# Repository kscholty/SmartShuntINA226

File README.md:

## Overview
This project uses an INA226 shunt amplifier to implement some smart shunt functionality.
It sums up the charges that move through the shunt. With this information it tries to calculate the load status of an attached battery.
The INA226 should be connected to the shunt so that charges going into the battery are positive and those coming out of the battery are negtive.

The smart shunt has three main interfaces.

1) A web interface for human users. It allows setting the main parameters of the system and displays the current status of the system
2) A modbus interface that is based on a PZEM017 energy meter but enhances it with the values mentioned above
3) Victron VE.direct Text and Hex protocols in order to function as a Battery Monitor. The Hex protocol is only implemented as far as it's required for startup. Furthermore, some fields of the Text protocol are not yet filled correctly.

## Building the code yourself
The Software has been created using platformio and the Arduino environment. In order to build it you als need some libraries.
* the [INA226lib](https://github.com/peterus/INA226Lib) The latest version should work with this code.
* emelianov/modbus-esp8266
* locoduino/RingBuffer
* prampec/IotWebConf

The latter three will be automatically downloaded when using platformio.

## Required hardware

For measuring the current you need an __INA226 breakout board__ as you can acquire from 
[Amazon](https://www.amazon.de/ALAMSCN-Bi-Directional-Voltage-Current-Monitoring/dp/B09Z66QSPB/ref=sr_1_4?keywords=ina226&qid=1674921078&sr=8-4),
[Ebay](https://www.ebay.de/itm/403798012528?mkcid=16&mkevt=1&mkrid=707-127634-2357-0&ssspo=3VTGCNeFTJm&sssrc=2047675&ssuid=0YZwUxrsQgu&widget_ver=artemis&media=COPY) or [AliExpress](https://de.aliexpress.com/item/1005001593541480.html?spm=a2g0o.productlist.main.3.56f351729HIcrL&algo_pvid=355d9f06-c6bf-45e7-922c-611aa36108cf&algo_exp_id=355d9f06-c6bf-45e7-922c-611aa36108cf-1&pdp_ext_f=%7B%22sku_id%22%3A%2212000016714954183%22%7D&pdp_npi=2%40dis%21EUR%213.22%212.06%21%21%21%21%21%402145294416749211574187658d06b7%2112000016714954183%21sea&curPageLogUid=PnWeLZQyi9Cc)

I noticed that some of the boards have a different pinout. The SDA and SDL pins are swapped in comparison to others. So please check this if you can't get a connection to the sensor.

As __miocrocontroller__ I settled for Espressif products. This code has been tested with a Wemos D1 Mini, a Wemos S2 mini and a 8266 Nodemcu. I didn't test any ESP32 WROOM boards, but they should work too. I setteled for the S2 mini due to its small footprint and powerful CPU. I got mine from [Aliexpress](https://de.aliexpress.com/item/1005004438665554.html?spm=a2g0o.productlist.main.5.5ffa60aafadABW&algo_pvid=dd20a2a6-e95b-45fa-a21f-18e0922615da&algo_exp_id=dd20a2a6-e95b-45fa-a21f-18e0922615da-2&pdp_ext_f=%7B%22sku_id%22%3A%2212000029182790427%22%7D&pdp_npi=2%40dis%21EUR%212.72%212.23%21%21%21%21%21%402145274c16754348326558450d06ca%2112000029182790427%21sea&curPageLogUid=wBPd7zKYNEX1)

You also need a __shunt__, since the small resistor on the board (dont forget to remove it!) will not survive the high currents of a PV plant.
There are plenty of options out there. Again [Aliexpress](https://de.aliexpress.com/item/1005001678592758.html?spm=a2g0o.productlist.main.29.306d4ec19gJkAJ&algo_pvid=29bbcfa0-d3c6-4854-8a79-1bb33adbf3d4&aem_p4p_detail=2023020306362112631641799161540004060030&algo_exp_id=29bbcfa0-d3c6-4854-8a79-1bb33adbf3d4-14&pdp_ext_f=%7B%22sku_id%22%3A%2212000017093083607%22%7D&pdp_npi=2%40dis%21EUR%213.88%213.1%21%21%21%21%21%402100b84516754349819031656d0753%2112000017093083607%21sea&curPageLogUid=4Pyd35DHXJ61&ad_pvid=2023020306362112631641799161540004060030_4&ad_pvid=2023020306362112631641799161540004060030_4) or [Ebay](https://www.ebay.de/sch/i.html?_from=R40&_trksid=p2334524.m570.l1313&_nkw=shunt+resistor&_sacat=0&LH_TitleDesc=0&_odkw=shunt&_osacat=0) are probably the best sources.
Make sure that you select a resistor appropriate for the currents you expect. I'm using a 200A/75mV shunt.

I recommend using a __buck converter__ to create 5V for feeding the MCU and the sensor from the battery. 
Make sure Battery - is connected to the GND potential of the sensor. Otherwise the voltage measurements will be invalid, since the INA226 has only one GND.
Furthermore, you should use an __isolated USB module__ to connect the D1 to the target. You can destroy your computer or Victron GSX if you connect it directly to the USB of the MCU. [I use this one](https://www.ebay.de/itm/164934927888?mkcid=16&mkevt=1&mkrid=707-127634-2357-0&ssspo=k80Mu6A-TbK&sssrc=2047675&ssuid=0YZwUxrsQgu&widget_ver=artemis&media=COPY)

__Before you can use the sensor board you have to remove the shunt resistor soldered to that board and instead use a bigger shunt, e.g. a 100A/75mV.__
Make sure that the shunt supports the current your system produces. You can set the parameters of the shunt in the web interface.
A wide variety of shunts can be found on EBay or other platforms.

If you have a 48V System, be aware of the fact that the INA226 does only support voltages up to 36V (40V max). You need a voltage divider to make shure your sensor is not destroyed. 
The code assumes that you use a __470KOhm and a 1MOhm__ resistor, measuring across the 1MOhm towards GND. `( + --470K-- --1M -- GND )` This should work for a 16S LifePO4 battery. The smaller you choose the small resistor in comparison to the bigger one, the more accurate the measurement will be.

The configuration field `Voltage calibration factor` can be used to calibrate the voltage reading of the sensor. Set it to `1000` and then simply divide the real battery voltage by the value the sensor shows and multiply it by `1000`. 
The same can be done for the current in the field `Current calibration factor`. If you entered the shunt resistance correctly, a value close to 1000 is expected here. Mine is 1028.5.

The following image shows how to connect the parts.

## Interfaces:

1) Web Interface. 
    The web interface is quite self explanatory. It contains values to configure the shunt you are using. 
    Furthermore some that have been inspired by the Victron SmartShunt. 
2) Victron Text and Hex Protocols. These are decirbed on the  Victron Website and are mainly useful for connecting to Victron Cerbos or othe GX devices.
    Victron Device Type allow to declare Smart Shunt as a monitor for external load or supply: DC load, wind/water turbine, car alternator...
4)  The Modbus interface
    The Modbus interface uses 9600 Buad 8N2. The following registers are exposed
    - Holding registers (the first 4 are the ones from a PZEM-017)
    ```
        0: High Voltage alarm Threshold (not functional at the moment)
        1: Low Voltage alarm Threshold (not functional at the moment)
        2: Modbus Address
        3: Shunt Value (Refer to table below) what the values mean
        4: Identifier (This register contains the ID 0xBF39D to distinguish it from other sensors)
        5: Set SOC (Can be used to set an SOC, e.g. after startup)
    ```
    - Input Registers (again the first 8 are identical to the PZEM-017, however, here the current and power can be negative)
    ```
        0: Bus Voltage
        1: Current
        2: PowerLow (power low word)
        3: PowerHigh (power high word)
        4: EnergyLow (Energy low word)
        5: EnergyHigh (Energy high word)
        6: HighVoltageAlarm status (Is high voltage alarm set, not yet functional)
        7: LowVoltageAlarm status (Is high voltage alarm set, not yet functional)
        8: TimeToGoLow (LowWord of timeToGo in Seconds)
        9: TimeToGoHigh (HighWord of timeToGo in Seconds)
        10: SOC (Soc in %)
        11: isFull (1 if battery is detected to be full, 0 otherwise)
    ```

Shunt values for modbus, assumed is a voltage of 75mV at nominal current. 
The values are those used by PZEM-017.

```
Register Value | nominal current | Resulting resistance mR
0              |  100A           |  0.750
1              |   50A           |  1.500
2              |  200A           |  0.375
3              |  300A           |  0.250
```

When you start the sensor for the first time it will open an access point you can connect to in order to set wifi credentials and the other parameters.
After connecting to that access point, direct your browser to `http://192.168.4.1`. This will open the configuration page.
The sensor will always create that access point after startup. For how long can be configured. 

## Screenshots

## Remote console with Shunt

## Remote console details

## Remote console details for DC system

## Real setup with SmartShunt as a DC System

## Web config

## Web config for Victron Device Type

## Everything soldered together

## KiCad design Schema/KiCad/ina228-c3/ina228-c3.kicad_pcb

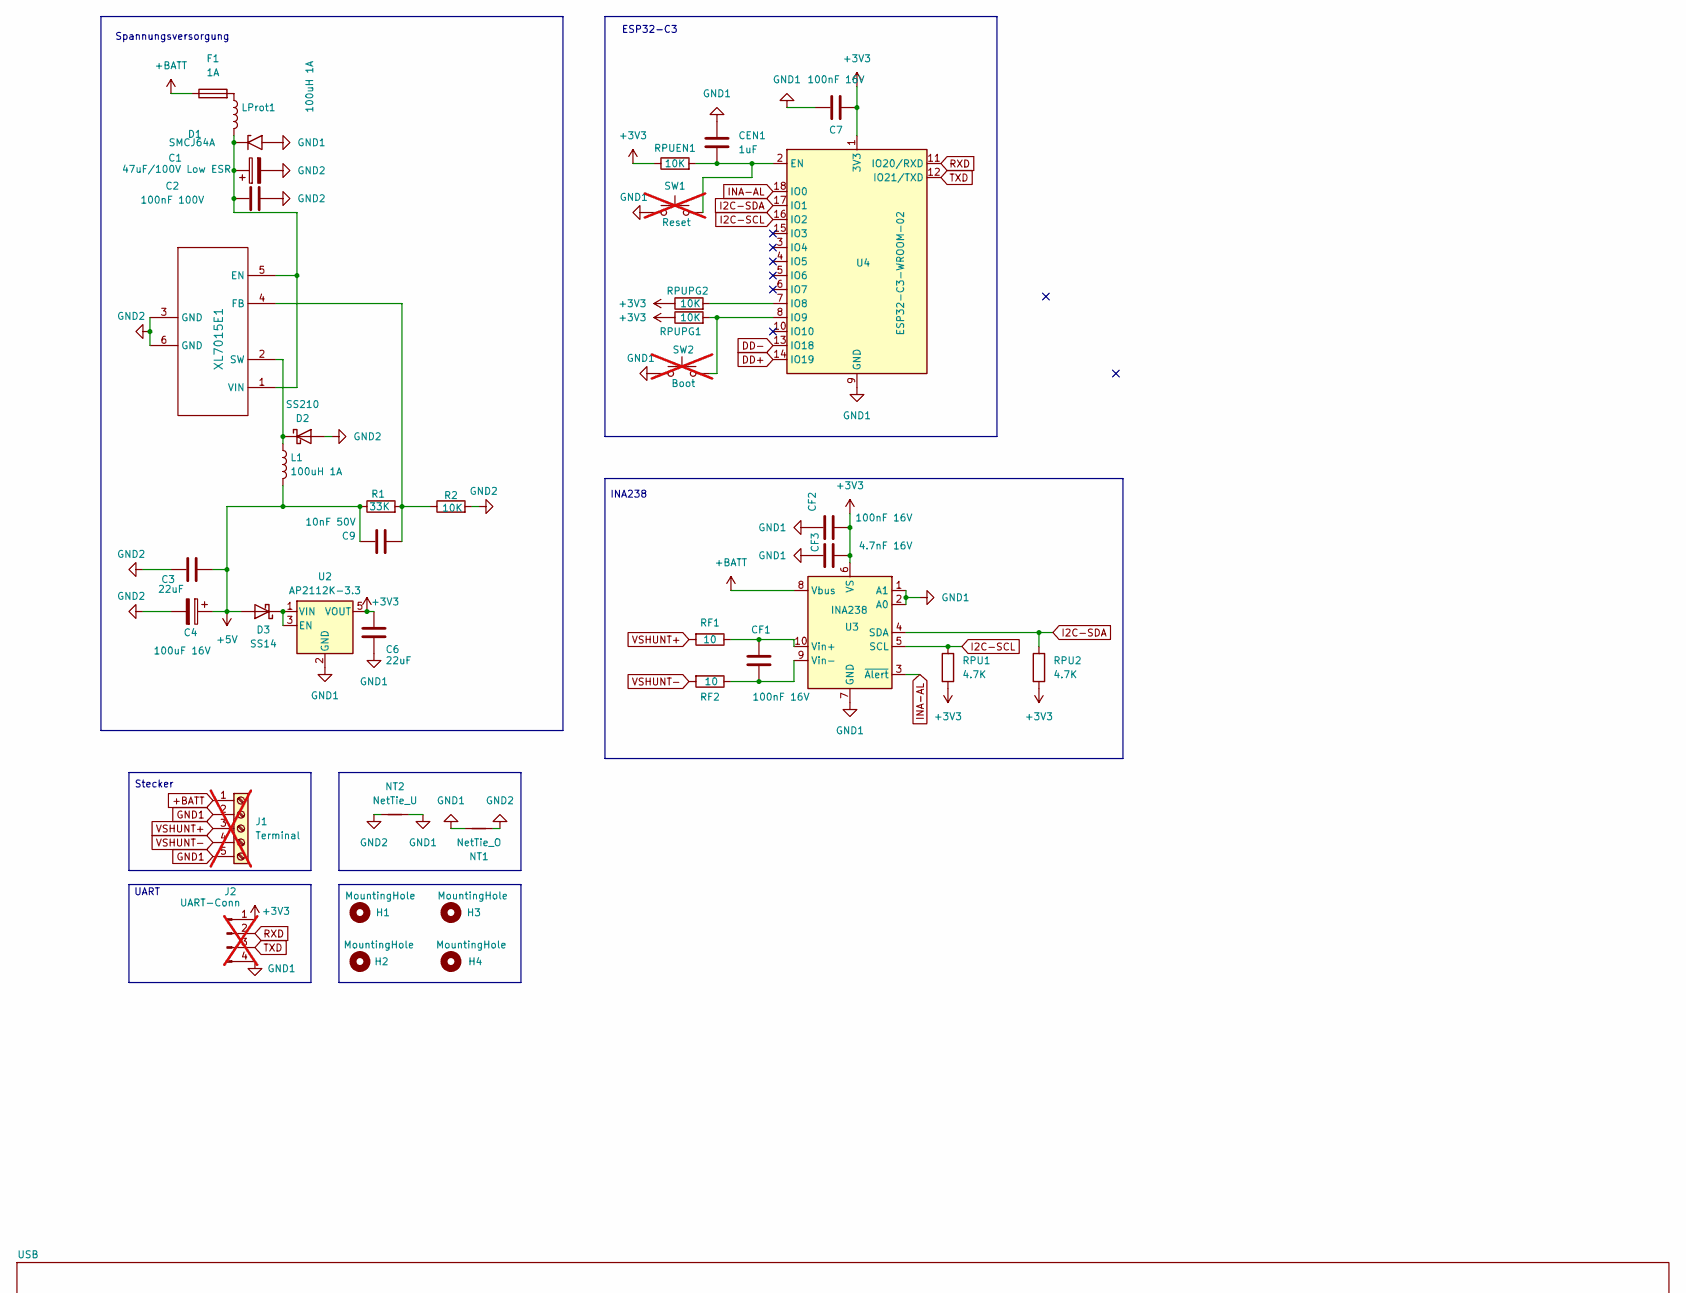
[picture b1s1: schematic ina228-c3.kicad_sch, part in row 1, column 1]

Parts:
C1: 47uF/100V Low ESR; CP_Elec_8x10.5; LCSC C22472101
C2: 100nF 100V; C_0805_2012Metric; LCSC C28233
C3: 22uF; C_1206_3216Metric; LCSC C12891
C4: 100uF 16V; CP_Elec_6.3x5.4; LCSC C2887276
C6: 22uF; C_0805_2012Metric; LCSC C45783
C7: 100nF 16V; C_0603_1608Metric; LCSC C14663
C9: 10nF 50V; C_0603_1608Metric; LCSC C57112
CEN1: 1uF; C_0603_1608Metric; LCSC C15849
CF1, CF2: 100nF 16V; C_0603_1608Metric; LCSC C14663
CF3: 4.7nF 16V; C_0603_1608Metric; LCSC C53987
D1: SMCJ64A; D_SMC; LCSC C5861053
D2: SS210; D_SMA; LCSC C14996
D3: SS14; D_SMA; LCSC C2480
F1: 1A; Fuse_1206_3216Metric; LCSC C52988549
H1, H2, H3, H4: MountingHole; MountingHole_2.2mm_M2_DIN965
J1: Terminal; PhoenixContact_MSTBA_2,5_5-G-5,08_1x05_P5.08mm_Horizontal; not fitted
J2: UART-Conn; PinHeader_1x04_P2.54mm_Vertical; not fitted
L1: 100uH 1A; L_TDK_VLS6045EX_VLS6045AF; LCSC C5339564
LProt1: 100uH 1A; L_TDK_VLS6045EX_VLS6045AF; LCSC C168137
NT1: NetTie_O; NetTie-2_SMD_Pad2.0mm
NT2: NetTie_U; NetTie-2_SMD_Pad2.0mm
R1: 33K; R_0603_1608Metric; LCSC C4216
R2: 10K; R_0603_1608Metric; LCSC C25804
RF1, RF2: 10; R_0603_1608Metric; LCSC C22859
RPU1, RPU2: 4.7K; R_0603_1608Metric; LCSC C23162
RPUEN1: 10K; R_0603_1608Metric; LCSC C25804
RPUPG1, RPUPG2: 10K; R_0603_1608Metric; LCSC C25804
SW1: Reset; SW_PUSH_1P1T_6x3.5mm_H4.3_APEM_MJTP1243; not fitted
SW2: Boot; SW_PUSH_1P1T_6x3.5mm_H4.3_APEM_MJTP1243; not fitted
U1: XL7015E1; TO-252-5_L6.6-W5.8-P1.27-TL; Manufacturer Part XL7015E1; LCSC C73013
U2: AP2112K-3.3; SOT-23-5; LCSC C23380830
U3: INA238; VSSOP-10_3x3mm_P0.5mm; LCSC C2868250
U4: ESP32-C3-WROOM-02; LCSC C2934560

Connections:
+3V3: C6.1, C7.1, CF2.2, CF3.2, J2.1, RPU1.2, RPU2.2, RPUEN1.1, RPUPG1.1, RPUPG2.1, U2.5 (VOUT), U3.6 (VS), U4.1 (3V3); also elsewhere on the board
+5V: C3.2, C4.1, C9.1, D3.2 (A), L1.2, R1.1
+BATT: F1.1, J1.1, U3.8 (Vbus)
DD+: U4.14 (IO19); also elsewhere on the board
DD-: U4.13 (IO18); also elsewhere on the board
GND1: C6.2, C7.2, CEN1.1, CF2.1, CF3.1, D1.2 (A2), J1.2, J1.5, J2.4, NT1.2, NT2.2, SW1.1, SW2.1, U2.2 (GND), U3.1 (A1), U3.2 (A0), U3.7 (GND), U4.9 (GND), U4.19 (GND); also elsewhere on the board
GND2: C1.2, C2.1, C3.1, C4.2, D2.2 (A), NT1.1, NT2.1, R2.2, U1.3 (GND), U1.6 (GND)
I2C-SCL: RPU1.1, U3.5 (SCL), U4.16 (IO2)
I2C-SDA: RPU2.1, U3.4 (SDA), U4.17 (IO1)
INA-AL: U3.3 (~Alert), U4.18 (IO0)
unnamed: C1.1, C2.2, D1.1 (A1), LProt1.2, U1.1 (VIN), U1.5 (EN)
unnamed: D2.1 (K), L1.1, U1.2 (SW)
unnamed: D3.1 (K), U2.1 (VIN), U2.3 (EN)
unnamed: F1.2, LProt1.1
unnamed: C9.2, R1.2, R2.1, U1.4 (FB)
unnamed: CF1.1, RF1.1, U3.10 (Vin+)
unnamed: CF1.2, RF2.1, U3.9 (Vin-)
unnamed: CEN1.2, RPUEN1.2, SW1.2, U4.2 (EN)
unnamed: RPUPG2.2, U4.7 (IO8)
unnamed: RPUPG1.2, SW2.2, U4.8 (IO9)
RXD: J2.2, U4.11 (IO20/RXD)
TXD: J2.3, U4.12 (IO21/TXD)
VSHUNT+: J1.3, RF1.2
VSHUNT-: J1.4, RF2.2

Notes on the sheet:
ESP32-C3
UART
INA238
Stecker
Spannungsversorgung

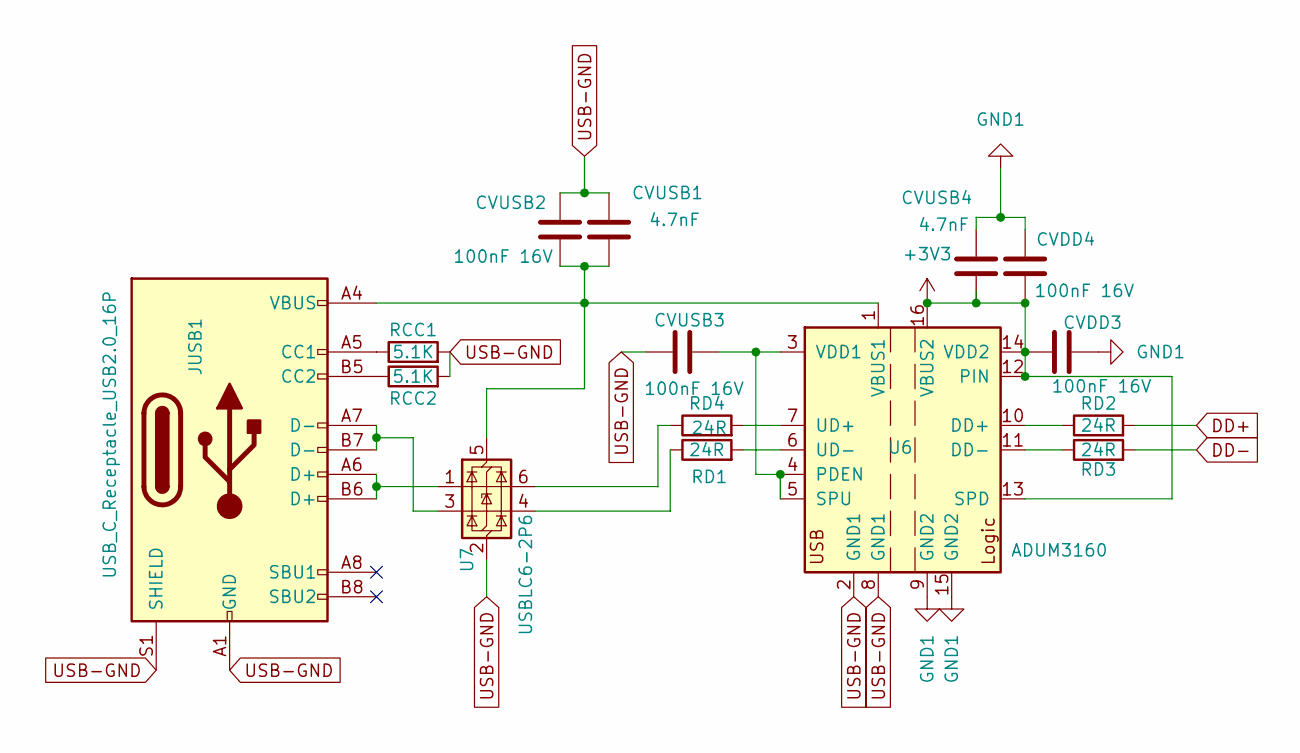
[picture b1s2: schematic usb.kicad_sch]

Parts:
CVDD3, CVDD4: 100nF 16V; C_0603_1608Metric; LCSC C14663
CVUSB1, CVUSB4: 4.7nF; C_0805_2012Metric; LCSC C1744
CVUSB2, CVUSB3: 100nF 16V; C_0603_1608Metric; LCSC C14663
JUSB1: USB_C_Receptacle_USB2.0_16P; USB_C_Receptacle_Palconn_UTC16-G; LCSC C393939
RCC1, RCC2: 5.1K; R_0603_1608Metric; LCSC C23186
RD1, RD2, RD3, RD4: 24R; R_0603_1608Metric; LCSC C4198
U6: ADUM3160; SOIC-16W_7.5x10.3mm_P1.27mm; Manufacturer Part CA-IS3741HW; LCSC C284149
U7: USBLC6-2P6; SOT-666; LCSC C2827693

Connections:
+3V3: CVDD3.1, CVDD4.1, CVUSB4.2, U6.12 (PIN), U6.13 (SPD), U6.14 (VDD2), U6.16 (VBUS2); also elsewhere on the board
DD+: RD2.2; also elsewhere on the board
DD-: RD3.2; also elsewhere on the board
GND1: CVDD3.2, CVDD4.2, CVUSB4.1, U6.9 (GND2), U6.15 (GND2); also elsewhere on the board
unnamed: JUSB1.A5 (CC1), RCC1.1
unnamed: JUSB1.B5 (CC2), RCC2.1
unnamed: JUSB1.A6 (D+), JUSB1.B6 (D+), U7.1 (I/O1)
unnamed: JUSB1.A7 (D-), JUSB1.B7 (D-), U7.3 (I/O2)
unnamed: RD1.1, U7.4 (I/O2)
unnamed: RD4.1, U7.6 (I/O1)
unnamed: RD2.1, U6.10 (DD+)
unnamed: RD3.1, U6.11 (DD-)
unnamed: CVUSB3.1, U6.3 (VDD1), U6.4 (PDEN), U6.5 (SPU)
unnamed: RD4.2, U6.7 (UD+)
unnamed: RD1.2, U6.6 (UD-)
unnamed: CVUSB1.2, CVUSB2.2, JUSB1.A4 (VBUS), JUSB1.A9 (VBUS), JUSB1.B4 (VBUS), JUSB1.B9 (VBUS), U6.1 (VBUS1), U7.5 (VBUS)
USB-GND: CVUSB1.1, CVUSB2.1, CVUSB3.2, JUSB1.A1 (GND), JUSB1.A12 (GND), JUSB1.B1 (GND), JUSB1.B12 (GND), JUSB1.S1 (SHIELD), RCC1.2, RCC2.2, U6.2 (GND1), U6.8 (GND1), U7.2 (GND)

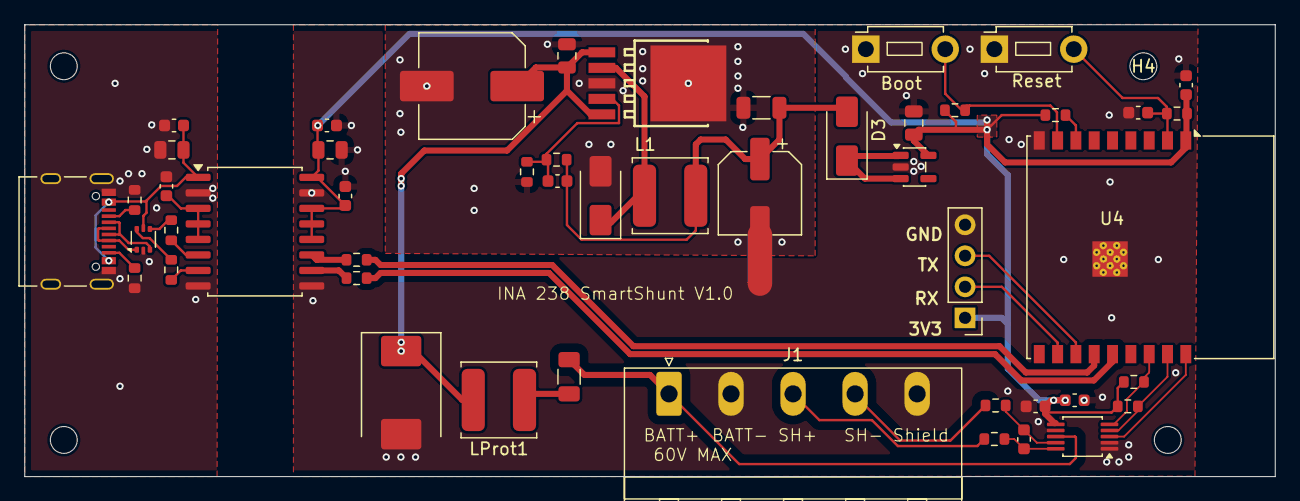
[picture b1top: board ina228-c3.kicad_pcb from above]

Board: 2 copper layers, 102.4 x 37.0 mm, 55 parts (1 on the bottom side), 37 nets.

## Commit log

2022-12-23 First implematation, not yet functional
2022-12-23 Modbus implemented
2022-12-23 All parts are working. Param translation not yet working...
2022-12-30 Changed parameters to typed and calling the conversion function
2022-12-30 Modbus is functional and parameters can be written Updated parameters are handled glidingAverage current is now correct.
2022-12-31 Implemented form to update SOC
2022-12-31 typos
2022-12-31 Now using 2 stopbits again. Removed debug output
2022-12-31 Full handling changed. SOm minoch cosmetic changes
2023-01-06 Updated handlingof sensor failure
2023-01-19 More Modbus registers, Runtime values (Currently only SOC) can be set from Web-GUI
2023-01-21 First functional version of VE-Direct HEX and TXT protocol This version shows up as a Smart Shunt
2023-01-28 Implemented Victron HEx and Text protocols as far as required. Not all History valkues are cortrrect yet.
2023-01-28 Changed order of includes to make sure it compiles with upstream INAlib
2023-01-28 Use more values to calculate TTG
2023-01-28 Some more documentation
2023-01-28 Added Schema
2023-01-28 Documentation updated
2023-01-29 Allow usage of ESP S2 Mini instead of D1 Mini Enhanced schematics
2023-01-29 Remove vscode file
2023-01-29 Added file
2023-02-02 More documentation Make sure statistrics update and victron update are in sync Schema updated
2023-02-03 Updated Reame.md
2023-02-03 Added Screenshots
2023-02-03 Some more images
2023-02-03 Bugfix in Readme.md
2023-02-03 Removed image
2023-02-03 Re-Uploaded file
2023-02-11 Fixed Min and Max voltage in stats storing statistics in RTC memory to survive resets Calibration factors fro vopltage an current
2023-02-15 Fixed tests in checkFull()
2023-12-03 Better handling of name
2024-03-14 Calibration values can now be set from the UI. Firmware updates from the webui Better handling of "full" detection
2025-11-20 Initial release
2025-11-20 Rename WebConfig.png to WebConfigOld.png
2025-11-20 Adding new screenshots for DC systems
2025-11-20 Updated ReadMe for new Device Type
2025-11-22 Changed AppId
    Issue #13
2026-02-19 Design with USB2UART chip
2026-02-22 Remove usb2uart chip, making the design simpler (but probably more expensive.)
